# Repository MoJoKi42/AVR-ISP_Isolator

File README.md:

# AVR-ISP_Isolator
Isolator Board for AVR ISP/SPI Programmers

Works well with the **AVR Dragon** and eBay **USB AVRISP** clones. With the buttons (relays) it's possible to disconnect the data and power lines from the external circuit. This is very useful if the SPI pins have multiple purposes. The external voltage can vary from 3 to 5V. (The large THT resistor is already designed into the kicad project. This resistor was necessary because the P-Ch. FET has a higher leakage than expected)

Isolator with AVR Dragon in a self-built housing

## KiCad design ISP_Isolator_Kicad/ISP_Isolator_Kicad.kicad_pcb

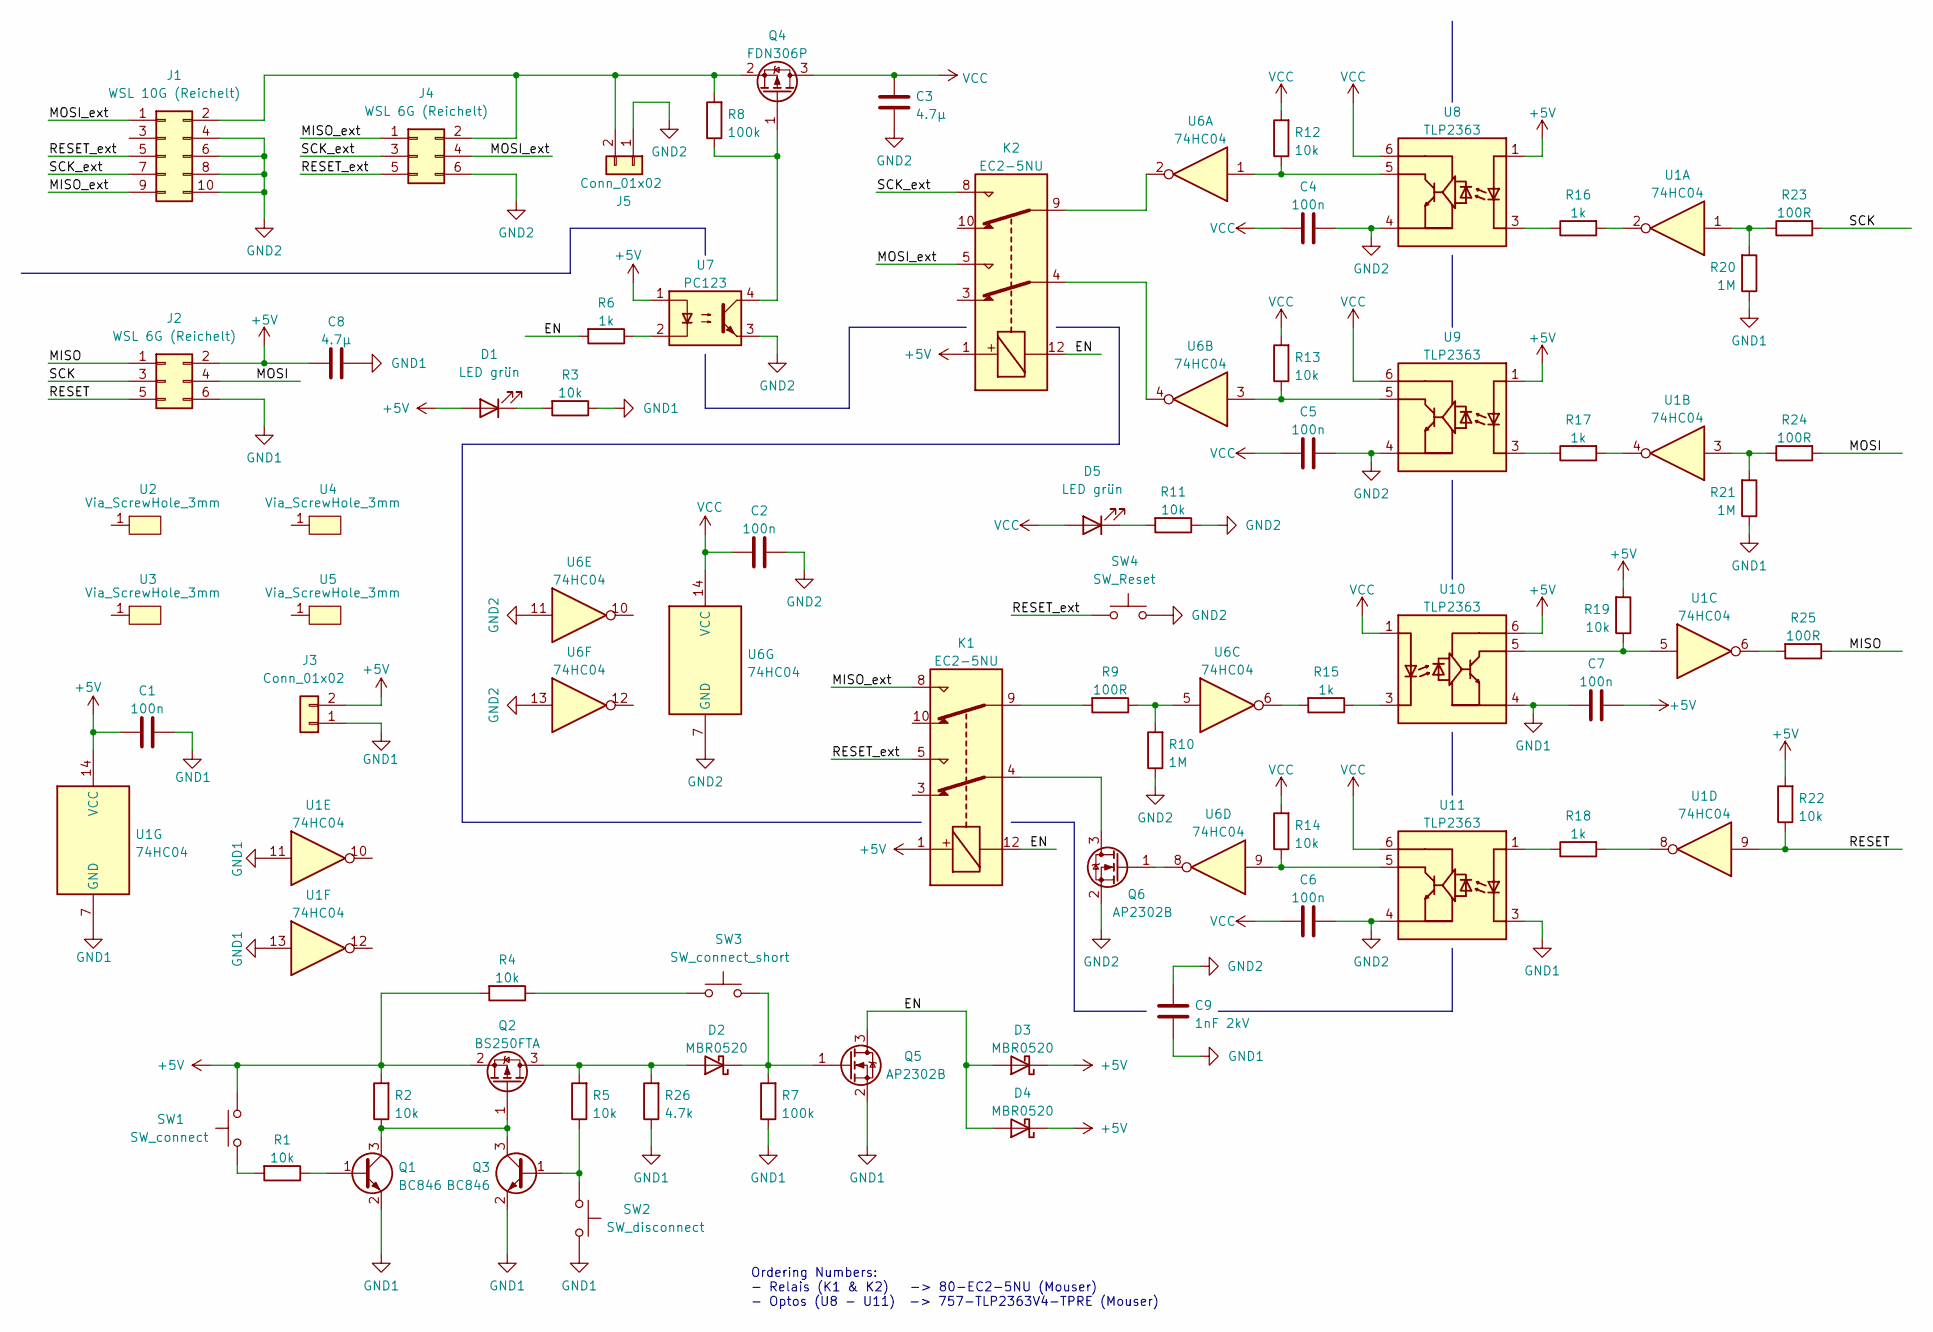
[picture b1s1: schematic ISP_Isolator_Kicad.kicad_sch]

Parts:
C1, C2, C4, C5, C6, C7: 100n; C_0805_2012Metric_Pad1.18x1.45mm_HandSolder
C3, C8: 4.7µ; C_1210_3225Metric_Pad1.33x2.70mm_HandSolder
C9: 1nF 2kV; C_1206_3216Metric_Pad1.33x1.80mm_HandSolder
D1, D5: LED grün; LED_PLCC-2_3.4x3.0mm_AK
D2, D3, D4: MBR0520; D_SOD-123
J1: WSL 10G (Reichelt); IDC-Header_2x05_P2.54mm_Vertical
J2, J4: WSL 6G (Reichelt); IDC-Header_2x03_P2.54mm_Vertical
J3, J5: Conn_01x02; PinHeader_1x02_P2.54mm_Vertical
K1, K2: EC2-5NU; Relay_DPDT_Kemet_EC2
Q1, Q3: BC846; SOT-23
Q2: BS250FTA; SOT-23
Q4: FDN306P; SOT-23
Q5, Q6: AP2302B; SOT-23
R1, R2, R3, R4, R5, R11, R12, R13, R14, R19, R22: 10k; R_0805_2012Metric_Pad1.20x1.40mm_HandSolder
R6, R15, R16, R17, R18: 1k; R_0805_2012Metric_Pad1.20x1.40mm_HandSolder
R7, R8: 100k; R_0805_2012Metric_Pad1.20x1.40mm_HandSolder
R9, R23, R24, R25: 100R; R_0805_2012Metric_Pad1.20x1.40mm_HandSolder
R10, R20, R21: 1M; R_0805_2012Metric_Pad1.20x1.40mm_HandSolder
R26: 4.7k; R_0805_2012Metric_Pad1.20x1.40mm_HandSolder
SW1: SW_connect; SW_Push_1P1T_NO_6x6mm_H9.5mm
SW2: SW_disconnect; SW_Push_1P1T_NO_6x6mm_H9.5mm
SW3: SW_connect_short; SW_Push_1P1T_NO_6x6mm_H9.5mm
SW4: SW_Reset; SW_Push_1P1T_NO_6x6mm_H9.5mm
U1, U6: 74HC04; SO-14_3.9x8.65mm_P1.27mm
U2, U3, U4, U5: Via_ScrewHole_3mm
U7: PC123; DIP-4_W7.62mm
U8, U9, U10, U11: TLP2363; SO-5_4.4x3.6mm_P1.27mm

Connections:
+5V: C1.1, C7.1, C8.1, D1.2 (A), D3.1 (K), D4.1 (K), J2.2, J3.2, K1.1, K2.1, Q2.2 (S), R2.2, R4.2, R19.2, R22.2, SW1.1, U1.14 (VCC), U7.1, U8.1, U9.1, U10.6
/EN: D3.2 (A), D4.2 (A), K1.12, K2.12, Q5.3 (D), R6.2
/MISO: J2.1, R25.1
/MISO_ext: J1.9, J4.1, K1.8
/MOSI: J2.4, R24.2
/MOSI_ext: J1.1, J4.4, K2.5
/RESET: J2.5, R22.1, U1.9
/RESET_ext: J1.5, J4.5, K1.5, SW4.2
/SCK: J2.3, R23.2
/SCK_ext: J1.7, J4.3, K2.8
GND1: C1.2, C7.2, C8.2, C9.2, J2.6, J3.1, Q1.2 (E), Q3.2 (E), Q5.2 (S), R3.1, R7.1, R20.1, R21.1, R26.1, SW2.2, U1.7 (GND), U1.11, U1.13, U10.4, U11.3
GND2: C2.2, C3.2, C4.2, C5.2, C6.2, C9.1, J1.4, J1.6, J1.8, J1.10, J4.6, J5.1, Q6.2 (S), R10.1, R11.1, SW4.1, U6.7 (GND), U6.11, U6.13, U7.3, U8.4, U9.4, U11.4
unnamed: D1.1 (K), R3.2
unnamed: D2.1 (K), Q5.1 (G), R7.2, SW3.1
unnamed: D5.1 (K), R11.2
unnamed: J1.2, J4.2, J5.2, Q4.2 (S), R8.2
unnamed: K1.4, Q6.3 (D)
unnamed: K1.9, R9.2
unnamed: K2.4, U6.4
unnamed: K2.9, U6.2
unnamed: Q1.1 (B), R1.1
unnamed: Q1.3 (C), Q2.1 (G), Q3.3 (C), R2.1
unnamed: D2.2 (A), Q2.3 (D), R5.2, R26.2
unnamed: Q3.1 (B), R5.1, SW2.1
unnamed: Q4.1 (G), R8.1, U7.4
unnamed: Q6.1 (G), U6.8
unnamed: R1.2, SW1.2
unnamed: R6.1, U7.2
unnamed: R9.1, R10.2, U6.5
unnamed: R12.1, U6.1, U8.5
unnamed: R13.1, U6.3, U9.5
unnamed: R14.1, U6.9, U11.5
unnamed: R15.1, U10.3
unnamed: R15.2, U6.6
unnamed: R16.1, U8.3
unnamed: R16.2, U1.2
unnamed: R17.1, U9.3
unnamed: R17.2, U1.4
unnamed: R18.1, U11.1
unnamed: R18.2, U1.8
unnamed: R19.1, U1.5, U10.5
unnamed: R20.2, R23.1, U1.1
unnamed: R21.2, R24.1, U1.3
unnamed: R25.2, U1.6
unnamed: R4.1, SW3.2
VCC: C2.1, C3.1, C4.1, C5.1, C6.1, D5.2 (A), Q4.3 (D), R12.2, R13.2, R14.2, U6.14 (VCC), U8.6, U9.6, U10.1, U11.6

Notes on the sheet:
Ordering Numbers: - Relais (K1 & K2) -> 80-EC2-5NU (Mouser) - Optos (U8 - U11) -> 757-TLP2363V4-TPRE (Mouser)

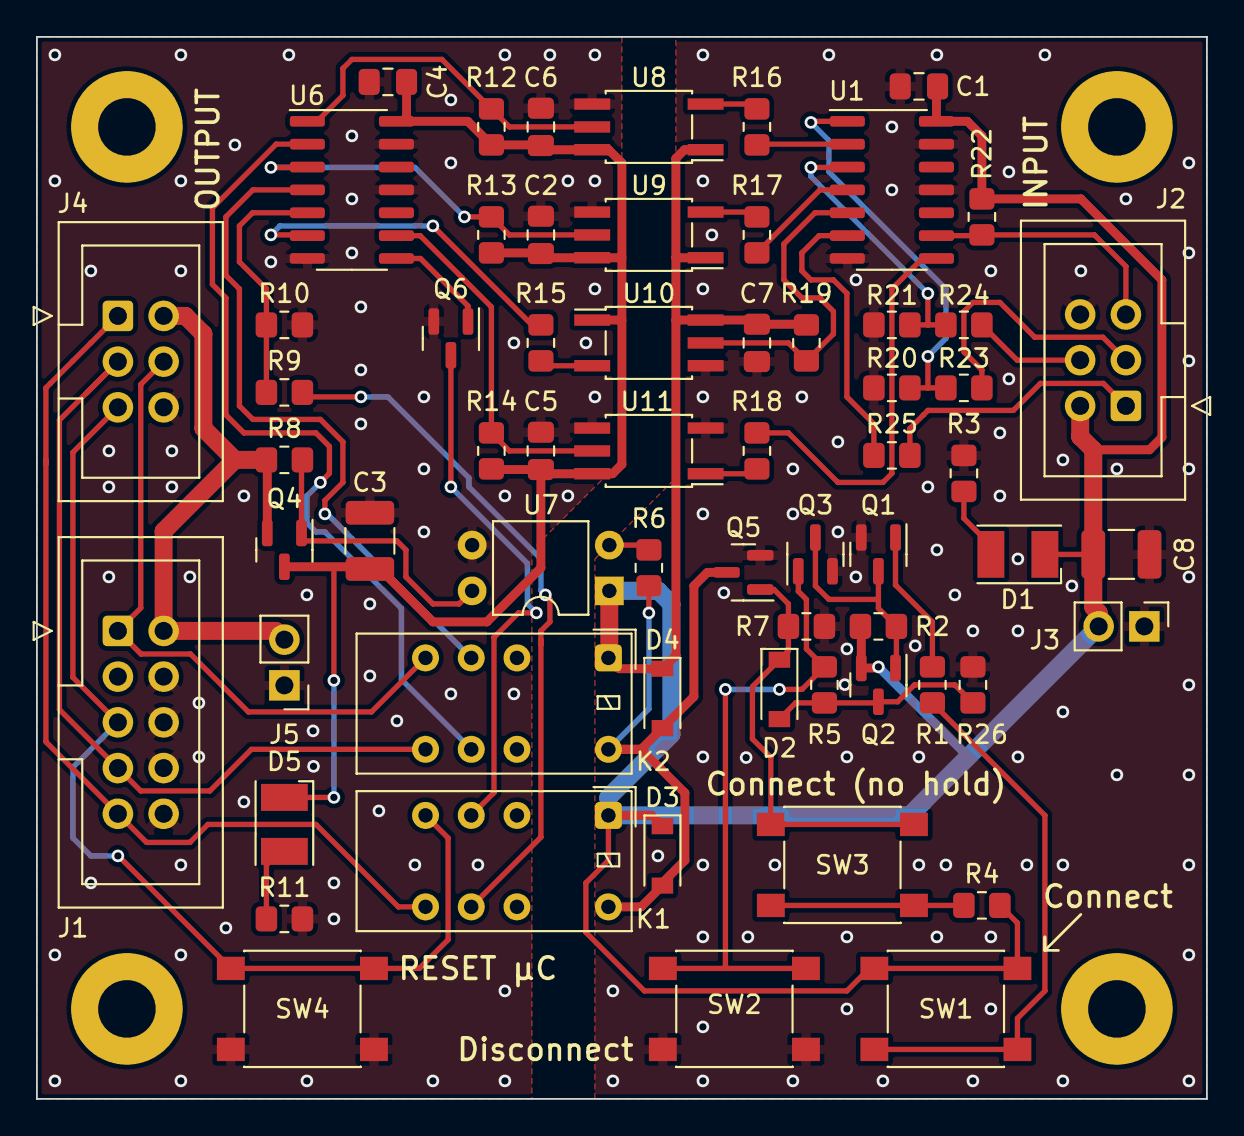
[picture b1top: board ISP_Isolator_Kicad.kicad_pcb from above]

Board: 2 copper layers, 65.0 x 59.0 mm, 68 parts (1 on the bottom side), 46 nets.

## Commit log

2023-08-03 init
